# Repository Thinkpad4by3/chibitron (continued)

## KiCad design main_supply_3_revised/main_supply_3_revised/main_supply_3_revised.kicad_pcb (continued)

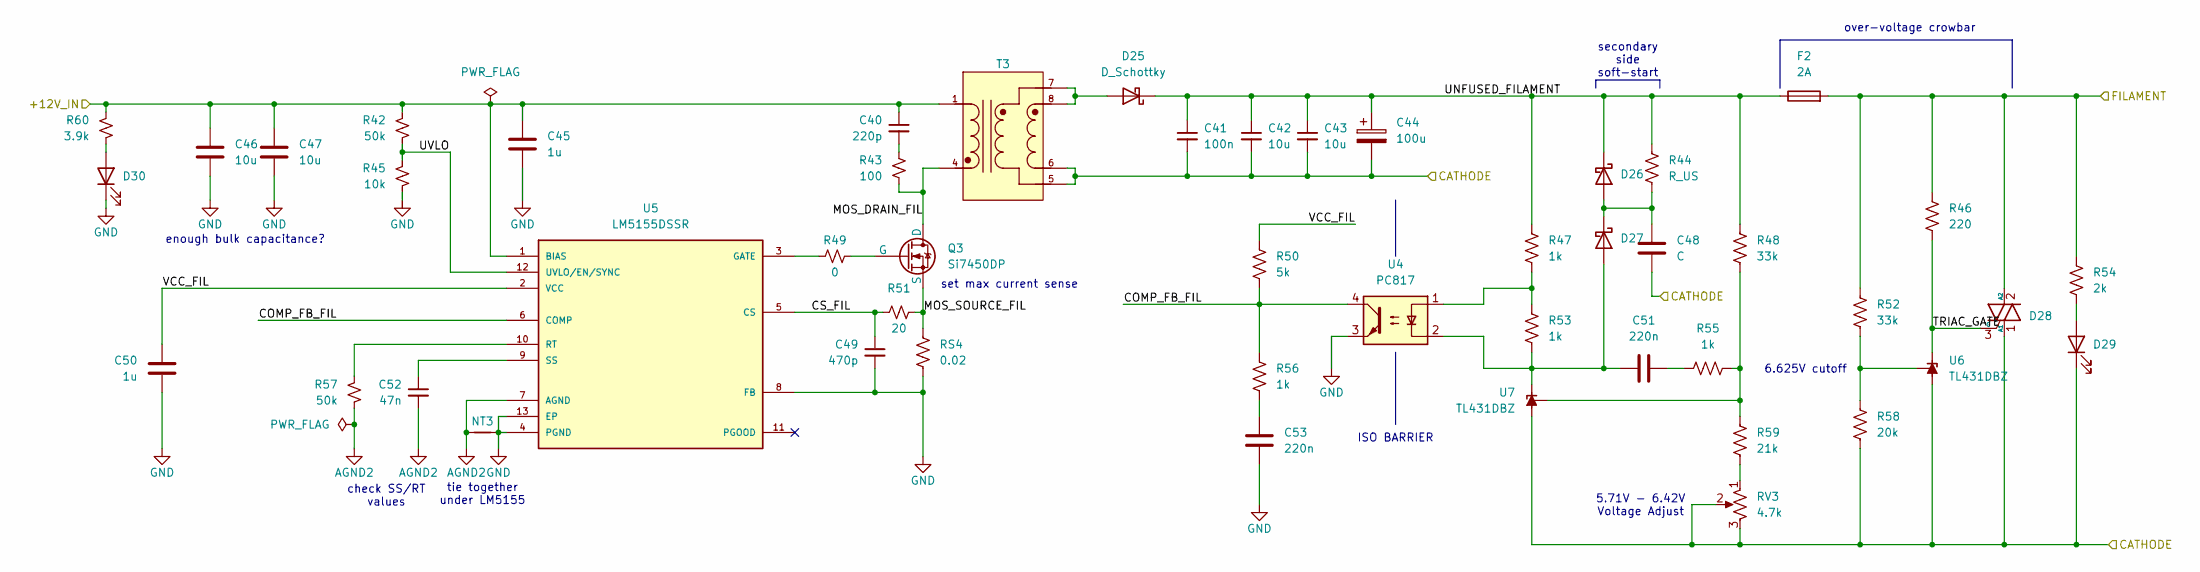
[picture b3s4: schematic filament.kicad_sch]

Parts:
C40: 220p; C_0603_1608Metric
C41: 100n; C_0603_1608Metric
C42, C43, C46, C47: 10u; C_0805_2012Metric
C44: 100u; CP_Elec_6.3x7.7
C45, C50: 1u; C_0603_1608Metric
C48: C; C_0603_1608Metric
C49: 470p; C_0603_1608Metric
C51, C53: 220n; C_0603_1608Metric
C52: 47n; C_0603_1608Metric
D25: D_Schottky; D_SMA
D26, D27: D_Schottky; D_SOD-123
D28: Generic_Triac_A1A2G; SOT-223
D29, D30: LED; LED_0603_1608Metric
F2: 2A; Fuseholder_Littelfuse_Nano2_154x
NT3: NetTie_2; NetTie-2_SMD_Pad0.5mm
Q3: Si7450DP; PowerPAK_SO-8_Single
R42, R57: 50k; R_0603_1608Metric
R43: 100; R_0603_1608Metric
R44: R_US; R_0603_1608Metric
R45: 10k; R_0603_1608Metric
R46: 220; R_0603_1608Metric
R47, R53, R55, R56: 1k; R_0603_1608Metric
R48, R52: 33k; R_0603_1608Metric
R49: 0; R_0603_1608Metric
R50: 5k; R_0603_1608Metric
R51: 20; R_0603_1608Metric
R54: 2k; R_0603_1608Metric
R58: 20k; R_0603_1608Metric
R59: 21k; R_0603_1608Metric
R60: 3.9k; R_0603_1608Metric
RS4: 0.02; R_1206_3216Metric
RV3: 4.7k; Potentiometer_Bourns_3296Y_Vertical
T3: YA9033-ALD; XFMR_YA9033-ALD; PARTREV 05/12/21
U4: PC817; DIP-4_W7.62mm
U5: LM5155DSSR; IC_LM5155DSSR; PARTREV E
U6, U7: TL431DBZ; SOT-23

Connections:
/Filament Supply/+12V_IN: C40.1, C45.1, C46.1, C47.1, R42.1, R60.1, T3.1, U5.1 (BIAS); also elsewhere on the board
/Filament Supply/CATHODE: C41.2, C42.2, C43.2, C44.2, C48.2, D28.1 (A1), D29.1 (K), R58.2, RV3.2, RV3.3, T3.5, T3.6, U6.3 (A), U7.3 (A); also elsewhere on the board
/Filament Supply/COMP_FB_FIL: R50.2, R56.1, U4.4, U5.6 (COMP)
/Filament Supply/CS_FIL: C49.1, R51.1, U5.5 (CS)
/Filament Supply/FILAMENT: D28.2 (A2), F2.2, R46.1, R52.1, R54.1; also elsewhere on the board
/Filament Supply/MOS_DRAIN_FIL: Q3.5 (D), R43.2, T3.4
/Filament Supply/MOS_SOURCE_FIL: Q3.1 (S), Q3.2 (S), Q3.3 (S), R51.2, RS4.1
/Filament Supply/TRIAC_GATE: D28.3 (G), R46.2, U6.1 (K)
/Filament Supply/UNFUSED_FILAMENT: C41.1, C42.1, C43.1, C44.1, D25.1 (K), D26.1 (K), F2.1, R44.1, R47.1, R48.1
/Filament Supply/UVLO: R42.2, R45.1, U5.12 (UVLO/EN/SYNC)
/Filament Supply/VCC_FIL: C50.1, R50.1, U5.2 (VCC)
AGND2: C52.2, NT3.1, R57.2, U5.7 (AGND)
GND: C45.2, C46.2, C47.2, C49.2, C50.2, C53.2, D30.1 (K), NT3.2, R45.2, RS4.2, U4.3, U5.4 (PGND), U5.8 (FB), U5.13 (EP); also elsewhere on the board
unnamed: C40.2, R43.1
unnamed: C51.2, R55.1
unnamed: C53.1, R56.2
unnamed: D25.2 (A), T3.7, T3.8
unnamed: C48.1, D26.2 (A), D27.1 (K), R44.2
unnamed: C51.1, D27.2 (A), R53.2, U4.2, U7.1 (K)
unnamed: D29.2 (A), R54.2
unnamed: D30.2 (A), R60.2
unnamed: Q3.4 (G), R49.2
unnamed: R47.2, R53.1, U4.1
unnamed: R59.2, RV3.1
unnamed: R49.1, U5.3 (GATE)
unnamed: R57.1, U5.10 (RT)
unnamed: C52.1, U5.9 (SS)
unnamed: R52.2, R58.1, U6.2 (REF)
unnamed: R48.2, R55.2, R59.1, U7.2 (REF)

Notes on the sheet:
set max current sense
tie together under LM5155
check SS/RT values
secondary side soft-start
ISO BARRIER
enough bulk capacitance?
6.625V cutoff
5.71V - 6.42V Voltage Adjust
over-voltage crowbar

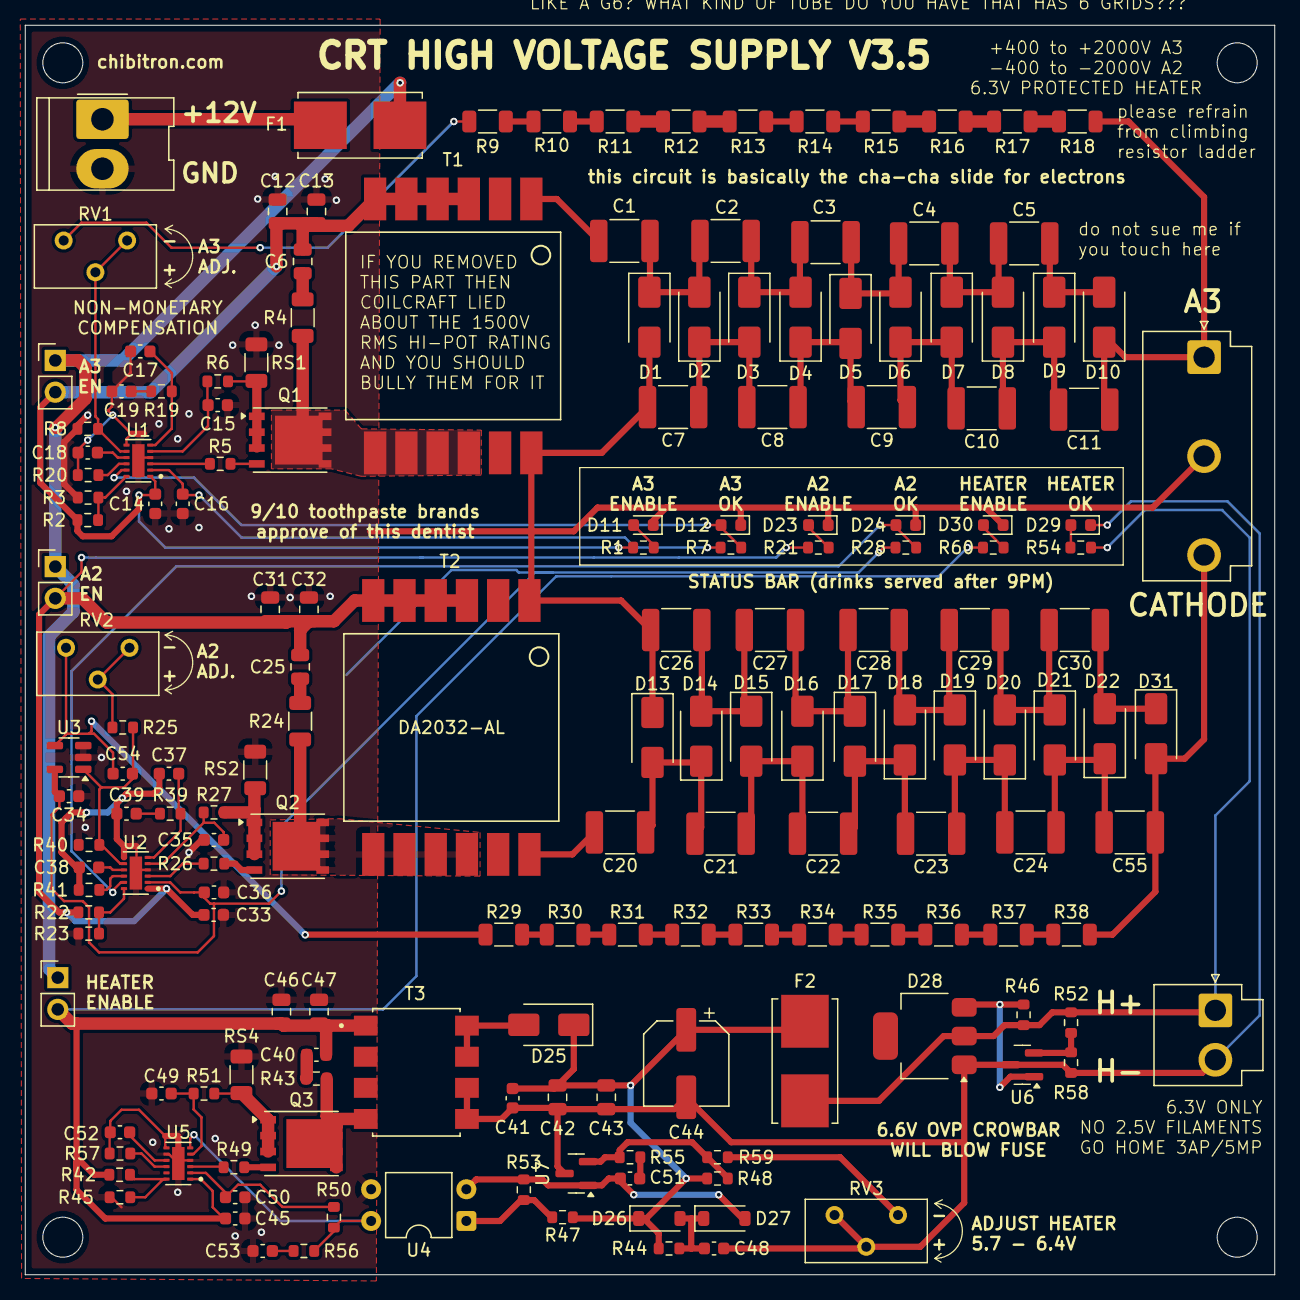
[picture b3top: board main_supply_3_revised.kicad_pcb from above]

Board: 2 copper layers, 100.0 x 100.0 mm, 176 parts (0 on the bottom side), 109 nets.

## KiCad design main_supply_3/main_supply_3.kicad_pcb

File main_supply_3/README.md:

## CRT High Voltage Gen.2 

## Status
- Completed, succeeded by main_supply_3_revised
- I would not recommend building this board

##  Design & Architecture 
The architecture was re-thought out from scratch over the previous supply. With the LM5180, they tended to work quite well, however they did have a bit of a major downside....regulation. Under extremely light load, the voltage would soar, and under very heavy load or it would tend to compensate by increasing the output voltage. Given the method of regulation is feedback sensing through the primary side, and high ratio step-up transformers are known for poor leakage inductance, the sensing ability of the converter could be quite poor at times. (See notes on Gen.1 V2 for more info on this)

Another reasons for ditching the LM5180 was due to was due to wanting variable output voltage, and the LM5180 uses a single resistor Rfb to determine this voltage. Not just did this require alot of tweaking, but provided no good method for changing the voltage with some level of signal control. Going back to a more conventional resistor divider style gave plenty of known proven options for this.

The new design uses an LM5155 and a far more conventional topology. The filament was powered through a TL431 regulated isolated flyback converter, and the A2/A3 generation was done through non-isolated ground referenced converters. A2 was referenced to ground, so the A2 supply generated the cathode potential at -400 - 2000V, and A3 was just the positive copy of A2. The main HV supplies use the NA5920-ALD, the only >1:10 ratio transformer available at the moment that is 

1) easily available
2) supports a >1000V HiPOT rating.

You might ask how I planned on getting 2000V out of a (barely) 1000V transformer. Well I'm going to use a voltage multiplier to just multiply the output by 3X. Seems like a good idea....cockroft-walton multipliers have been a proven choice of high-voltage generation for nearly a century. Well, we will get back to this in a bit. The exact topology follows the "boost mode style" found in a few LiDAR supplies and the like, which means that the charge pump caps are seperate from the filter caps, and the filter caps are larger. Otherwise, it operates the same way. Rough calculations say that 3x multiplier @ 2000V should keep the primary side at ~700V even at max voltage, should be fine for a 1500Vrms rated transformer. Primary side spiking thanks to the large 1:24 ratio would be kept at a meager 30V which would allow the choice of some more common low-voltage FETs.

Focus Amplifier was a somewhat odd design. As found on previous designs, the standard focus ladder stack was limiting for larger tubes. The highest voltage potentiometer easily available is 500V, and some larger tubes (7JP/7VP series) takes nearly 1kV on A1. The design was tested in LTspice, and validated in circuit. I did revise it for the next version, since the method of creating an isolated voltage was quite convoluted and featured poor regulation as beam current increased. It was beneficial that the focus voltage was now on the primary side, low voltage control.

## Troubleshooting & Bring-up 
The bring-up of this supply was quite troublesome. The main issue being that I did not realize the true nature of voltage-multiplied flybacks, being that they conduct on both halves of the cycle. This becomes a much bigger problem when you realize that reflected impedance is squared of the turns ratio, so the 12mA or so peak current on the secondary side becomes almost 7A on the primary side. The converter, running in current mode control, sees 7A and immediately trips, so it fails to actually regulate anything and just kinda bubbles with tiny little bursts. This is enough to get to sort of develop and open-load voltage but under load it just dies. 

To combat this, I dug up my transformer stock and found some 1:10 that would just about fit in its place. This would reduce my primary current during the forward mode of the supply to 1.2A, which was enough to sneak it past the 4A primary side current limit. Regulation still wasn't great, as evidenced by the screaming sound the supply made, but was able to supply 2W to a 2Mohm load which was excellent. Further tweaking of R/C COMP values helped. 

Among the main fault, a bunch of small issues that I found include the following:

- Wrong value resistors for the feedback chain for 400-2.1kV - A2
- Increase soft-start capacitance
- Transformer wrong: switch to Wurth 10:1 part
- MOSFET too low voltage: need >200V part
- Fix layout to not have GND overlapping underneath transformer
- Add RC filtering to A2,A3 + LC filtering to Filament
- Change TLV314 to TLV237, check >6.8V operation
- Fix the 20 ohm resistors in the VM’s to be in the correct spot
- Add soft start to filament supply 
- Capacitively couple feedback -> test this (only on A3)
- Change the RC filtering?? 2/2n + 100ohm & 1k R slope comp.
- Change connectors and remove focus amp from power supply side.
- Re-layout and silkscreen
- Add large input cap and filtering 
- UVLO resistors configured incorrectly to disable on low-voltage - 10k lower
- Fix diode on filament to be Schottky not HV rectifier
- Add 220n + 2k resistor on A2
- Add interlock if no power to op amp -> no A2 supply?
- ADD POWER TO THE AMPLIFIER FOR A2 FEEDBACK
- Wrong sense resistor values for Current sense - 0.02ohm
- Wrong value resistors for the feedback chain for 400-2.1kV - A3
- Opto feedback wired up wrong - fix

## Learnings
Hugely better understand of secondary side regulated Flyback converters and voltage multipliers

Output needs to be filtered 

Class-A style focus amp works great

Good architecture, continue developing.

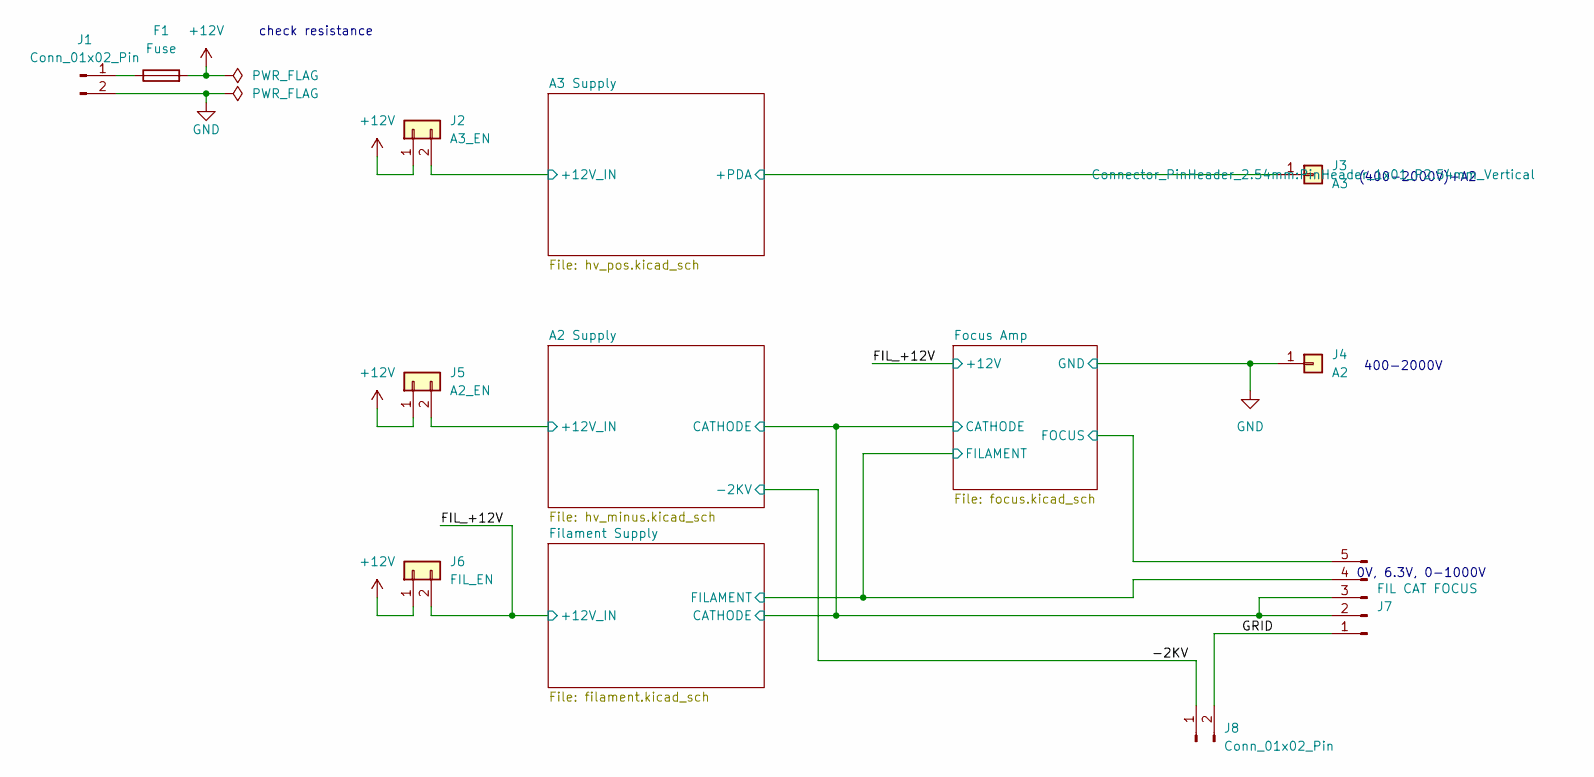
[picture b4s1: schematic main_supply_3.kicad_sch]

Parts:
F1: Fuse; Fuse_0805_2012Metric
J1: Conn_01x02_Pin; Molex_KK-396_5273-02A_1x02_P3.96mm_Vertical
J2: A3_EN; PinHeader_1x02_P2.54mm_Vertical
J3: A3; PinHeader_1x01_P2.54mm_Vertical
J4: A2; PinHeader_1x01_P2.54mm_Vertical
J5: A2_EN; PinHeader_1x02_P2.54mm_Vertical
J6: FIL_EN; PinHeader_1x02_P2.54mm_Vertical
J7: FIL CAT FOCUS; Molex_KK-396_5273-05A_1x05_P3.96mm_Vertical
J8: Conn_01x02_Pin; PinHeader_1x02_P2.54mm_Vertical

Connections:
+12V: F1.2, J2.1, J5.1, J6.1
/-2KV: J8.1; also elsewhere on the board
/A2 Supply/+12V_IN: J5.2; also elsewhere on the board
/A2 Supply/CATHODE: J7.2, J7.3; also elsewhere on the board
/A3 Supply/+12V_IN: J2.2; also elsewhere on the board
/A3 Supply/+PDA: J3.1; also elsewhere on the board
/FIL_+12V: J6.2; also elsewhere on the board
/Filament Supply/FILAMENT: J7.4; also elsewhere on the board
/Focus Amp/FOCUS: J7.5; also elsewhere on the board
/GRID: J7.1, J8.2
GND: J1.2, J4.1; also elsewhere on the board
unnamed: F1.1, J1.1

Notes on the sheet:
(400-2000V)+A2
400-2000V
0V, 6.3V, 0-1000V
check resistance

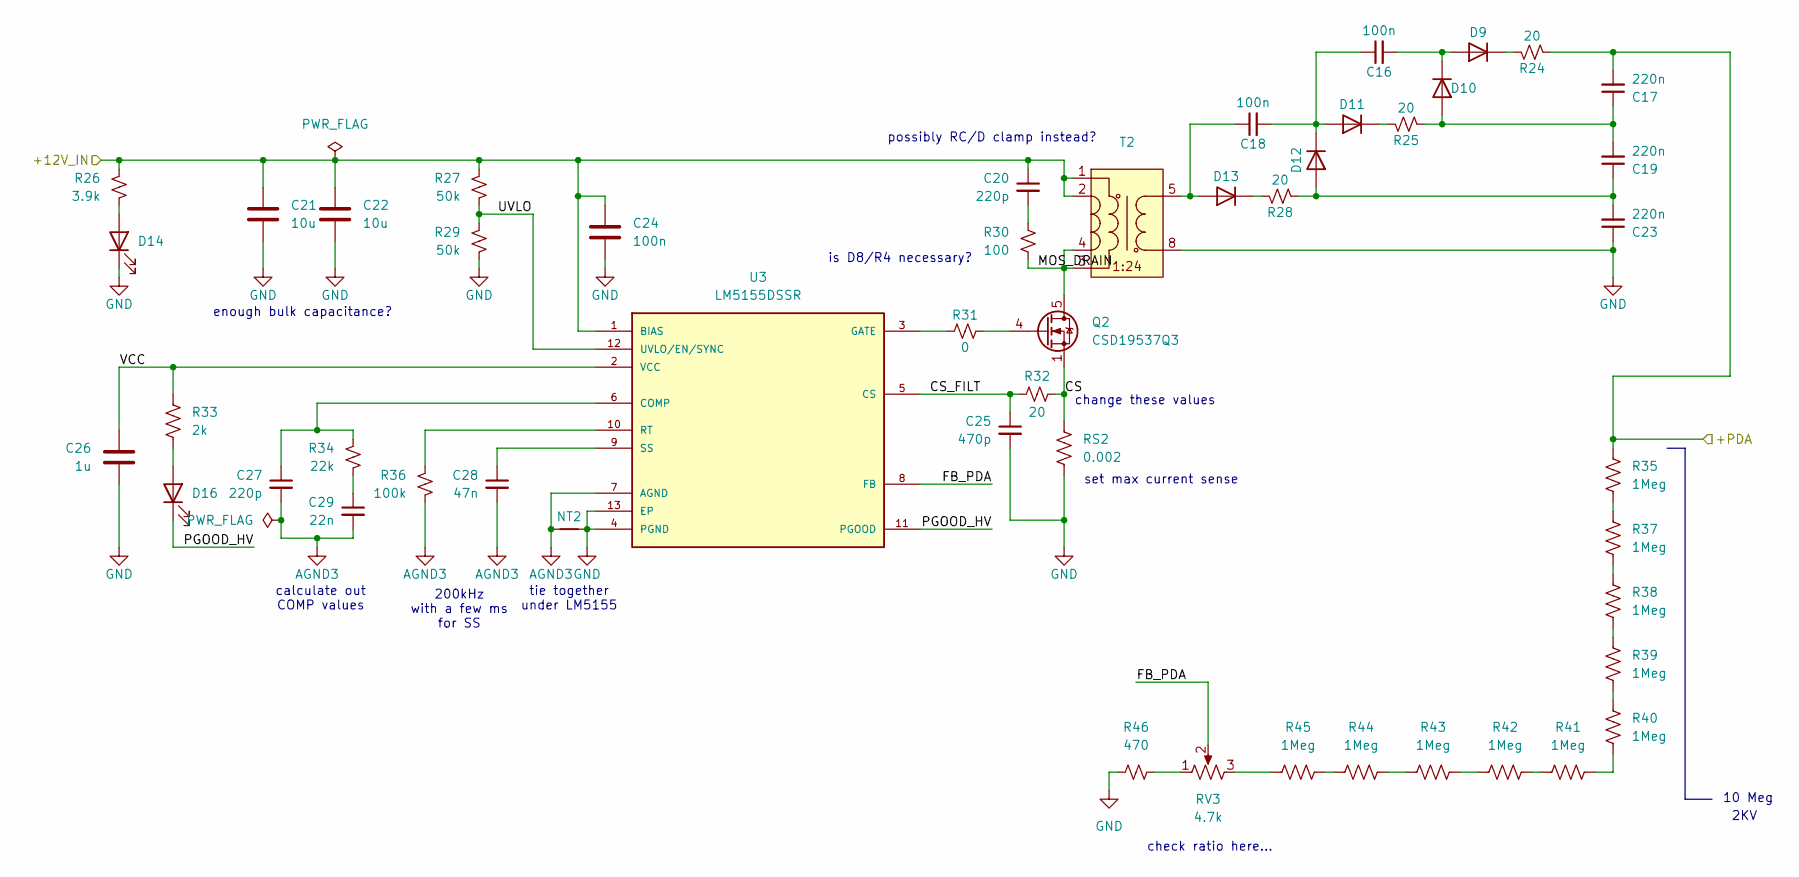
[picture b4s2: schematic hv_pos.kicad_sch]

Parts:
C16, C18: 100n; C_1812_4532Metric
C17, C19, C23: 220n; C_2220_5750Metric
C20, C27: 220p; C_0603_1608Metric
C21, C22: 10u; C_0805_2012Metric
C24: 100n; C_0603_1608Metric
C25: 470p; C_0603_1608Metric
C26: 1u; C_0603_1608Metric
C28: 47n; C_0603_1608Metric
C29: 22n; C_0603_1608Metric
D9, D10, D11, D12, D13: D; D_SMA
D14, D16: LED; LED_0603_1608Metric
NT2: NetTie_2; NetTie-2_SMD_Pad0.5mm
Q2: CSD19537Q3; VSON-8_3.3x3.3mm_P0.65mm_NexFET
R24, R25, R28: 20; R_1206_3216Metric
R26: 3.9k; R_0603_1608Metric
R27, R29: 50k; R_0603_1608Metric
R30: 100; R_0603_1608Metric
R31: 0; R_0603_1608Metric
R32: 20; R_0603_1608Metric
R33: 2k; R_0603_1608Metric
R34: 22k; R_0603_1608Metric
R35, R37, R38, R39, R40, R41, R42, R43, R44, R45: 1Meg; R_1206_3216Metric
R36: 100k; R_0603_1608Metric
R46: 470; R_0603_1608Metric
RS2: 0.002; R_1206_3216Metric
RV3: 4.7k; Potentiometer_Bourns_3296W_Vertical
T2: NA5920-AL
U3: LM5155DSSR; IC_LM5155DSSR; PARTREV E

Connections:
/A3 Supply/+12V_IN: C20.1, C21.1, C22.1, C24.1, R26.1, R27.1, T2.1, T2.2, U3.1 (BIAS); also elsewhere on the board
/A3 Supply/+PDA: C17.2, R24.2, R35.1; also elsewhere on the board
/A3 Supply/CS: Q2.1 (S), Q2.2 (S), Q2.3 (S), R32.2, RS2.1
/A3 Supply/CS_FILT: C25.1, R32.1, U3.5 (CS)
/A3 Supply/FB_PDA: RV3.2, U3.8 (FB)
/A3 Supply/MOS_DRAIN: Q2.5 (D), R30.2, T2.3, T2.4
/A3 Supply/PGOOD_HV: D16.1 (K), U3.11 (PGOOD)
/A3 Supply/UVLO: R27.2, R29.1, U3.12 (UVLO/EN/SYNC)
/A3 Supply/VCC: C26.1, R33.1, U3.2 (VCC)
AGND3: C27.2, C28.2, C29.2, NT2.1, R36.2, U3.7 (AGND)
GND: C21.2, C22.2, C23.1, C24.2, C25.2, C26.2, D14.1 (K), NT2.2, R29.2, R46.1, RS2.2, T2.8, U3.4 (PGND), U3.13 (EP); also elsewhere on the board
unnamed: C20.2, R30.1
unnamed: C29.1, R34.2
unnamed: D9.1 (K), R24.1
unnamed: C17.1, C19.2, D10.2 (A), R25.2
unnamed: C16.2, D9.2 (A), D10.1 (K)
unnamed: C16.1, C18.2, D11.2 (A), D12.1 (K)
unnamed: D11.1 (K), R25.1
unnamed: C19.1, C23.2, D12.2 (A), R28.2
unnamed: C18.1, D13.2 (A), T2.5
unnamed: D13.1 (K), R28.1
unnamed: D14.2 (A), R26.2
unnamed: D16.2 (A), R33.2
unnamed: Q2.4 (G), R31.2
unnamed: R35.2, R37.1
unnamed: R37.2, R38.1
unnamed: R38.2, R39.1
unnamed: R39.2, R40.1
unnamed: R40.2, R41.2
unnamed: R41.1, R42.2
unnamed: R42.1, R43.2
unnamed: R43.1, R44.2
unnamed: R44.1, R45.2
unnamed: R45.1, RV3.3
unnamed: R46.2, RV3.1
unnamed: C27.1, R34.1, U3.6 (COMP)
unnamed: R31.1, U3.3 (GATE)
unnamed: R36.1, U3.10 (RT)
unnamed: C28.1, U3.9 (SS)

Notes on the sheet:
check ratio here...
2KV
enough bulk capacitance?
calculate out COMP values
is D8/R4 necessary?
possibly RC/D clamp instead?
10 Meg
tie together under LM5155
change these values
set max current sense
200kHz with a few ms for SS

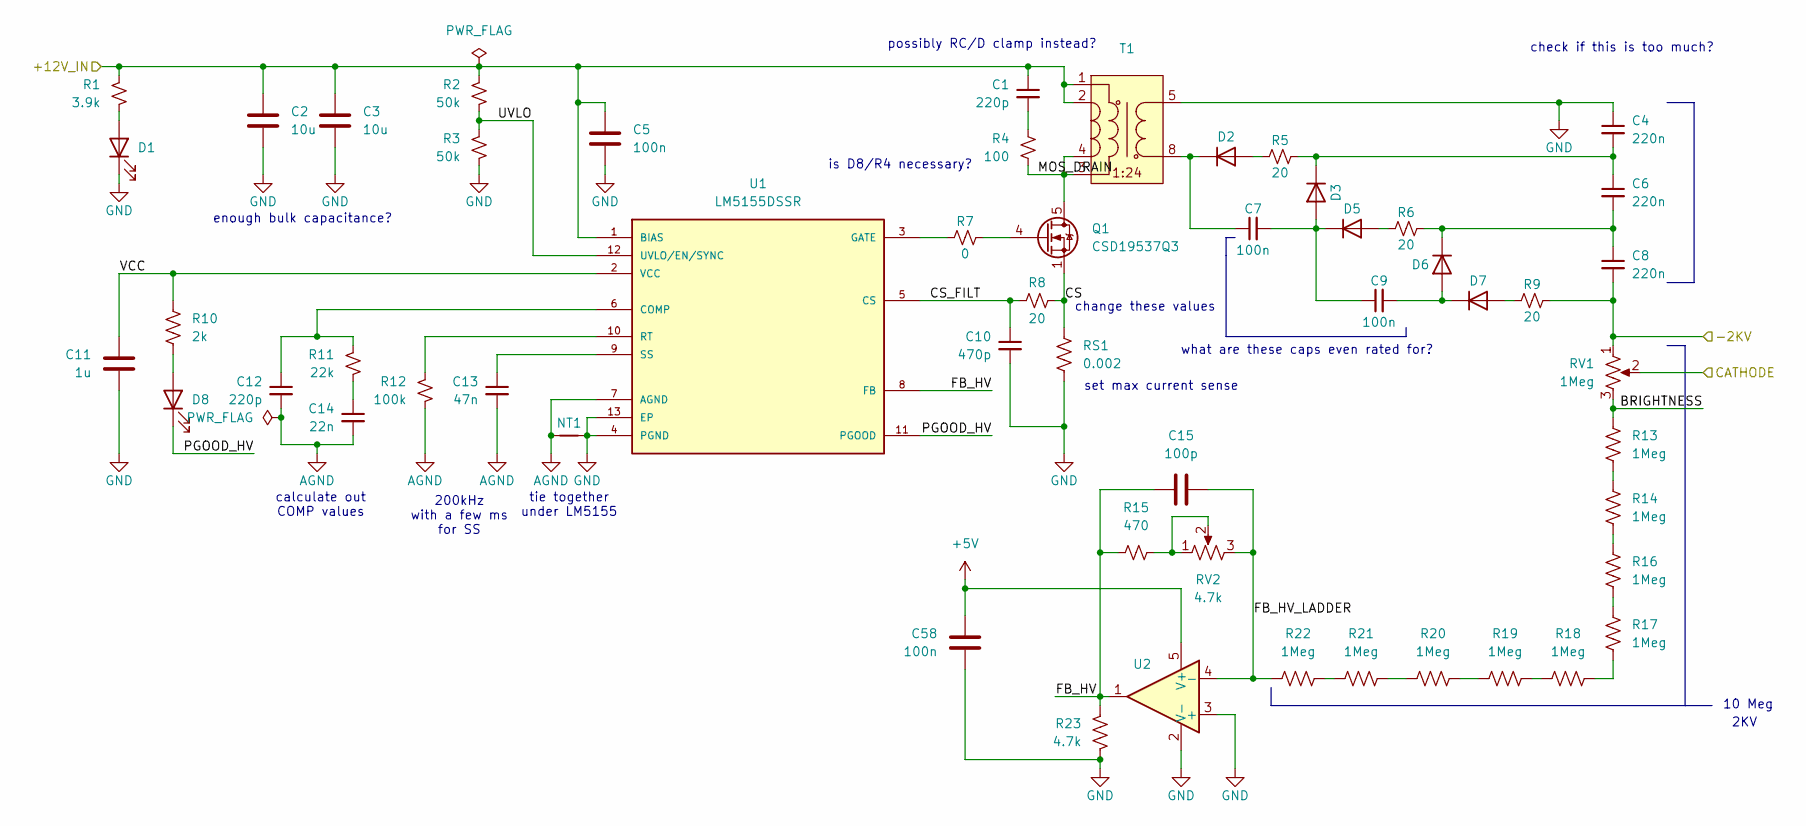
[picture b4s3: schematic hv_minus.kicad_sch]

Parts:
C1, C12: 220p; C_0603_1608Metric
C2, C3: 10u; C_0805_2012Metric
C4, C6, C8: 220n; C_2220_5750Metric
C5, C58: 100n; C_0603_1608Metric
C7, C9: 100n; C_1812_4532Metric
C10: 470p; C_0603_1608Metric
C11: 1u; C_0603_1608Metric
C13: 47n; C_0603_1608Metric
C14: 22n; C_0603_1608Metric
C15: 100p; C_0603_1608Metric
D1, D8: LED; LED_0603_1608Metric
D2, D3, D5, D6, D7: D; D_SMA
NT1: NetTie_2; NetTie-2_SMD_Pad0.5mm
Q1: CSD19537Q3; VSON-8_3.3x3.3mm_P0.65mm_NexFET
R1: 3.9k; R_0603_1608Metric
R2, R3: 50k; R_0603_1608Metric
R4: 100; R_0603_1608Metric
R5, R6, R9: 20; R_1206_3216Metric
R7: 0; R_0603_1608Metric
R8: 20; R_0603_1608Metric
R10: 2k; R_0603_1608Metric
R11: 22k; R_0603_1608Metric
R12: 100k; R_0603_1608Metric
R13, R14, R16, R17, R18, R19, R20, R21, R22: 1Meg; R_1206_3216Metric
R15: 470; R_0603_1608Metric
R23: 4.7k; R_0603_1608Metric
RS1: 0.002; R_1206_3216Metric
RV1: 1Meg; Potentiometer_Bourns_3296W_Vertical
RV2: 4.7k; Potentiometer_Bourns_3296W_Vertical
T1: NA5920-AL
U1: LM5155DSSR; IC_LM5155DSSR; PARTREV E
U2: TLV314QDBVR; SOT-23-5

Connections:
+5V: C58.1, U2.5 (V+); also elsewhere on the board
/-2KV: C8.2, R9.2, RV1.1; also elsewhere on the board
/A2 Supply/+12V_IN: C1.1, C2.1, C3.1, C5.1, R1.1, R2.1, T1.1, T1.2, U1.1 (BIAS); also elsewhere on the board
/A2 Supply/BRIGHTNESS: R13.1, RV1.3
/A2 Supply/CATHODE: RV1.2; also elsewhere on the board
/A2 Supply/CS: Q1.1 (S), Q1.2 (S), Q1.3 (S), R8.2, RS1.1
/A2 Supply/CS_FILT: C10.1, R8.1, U1.5 (CS)
/A2 Supply/FB_HV: C15.1, R15.1, R23.1, U1.8 (FB), U2.1
/A2 Supply/FB_HV_LADDER: C15.2, R22.1, RV2.3, U2.4 (-)
/A2 Supply/MOS_DRAIN: Q1.5 (D), R4.2, T1.3, T1.4
/A2 Supply/PGOOD_HV: D8.1 (K), U1.11 (PGOOD)
/A2 Supply/UVLO: R2.2, R3.1, U1.12 (UVLO/EN/SYNC)
/A2 Supply/VCC: C11.1, R10.1, U1.2 (VCC)
AGND: C12.2, C13.2, C14.2, NT1.1, R12.2, U1.7 (AGND)
GND: C2.2, C3.2, C4.1, C5.2, C10.2, C11.2, C58.2, D1.1 (K), NT1.2, R3.2, R23.2, RS1.2, T1.5, U1.4 (PGND), U1.13 (EP), U2.2 (V-), U2.3 (+); also elsewhere on the board
unnamed: C1.2, R4.1
unnamed: C14.1, R11.2
unnamed: D1.2 (A), R1.2
unnamed: D2.2 (A), R5.1
unnamed: C7.1, D2.1 (K), T1.8
unnamed: C7.2, C9.1, D3.2 (A), D5.1 (K)
unnamed: C4.2, C6.1, D3.1 (K), R5.2
unnamed: D5.2 (A), R6.1
unnamed: C9.2, D6.2 (A), D7.1 (K)
unnamed: C6.2, C8.1, D6.1 (K), R6.2
unnamed: D7.2 (A), R9.1
unnamed: D8.2 (A), R10.2
unnamed: Q1.4 (G), R7.2
unnamed: R13.2, R14.1
unnamed: R14.2, R16.1
unnamed: R15.2, RV2.1, RV2.2
unnamed: R16.2, R17.1
unnamed: R17.2, R18.2
unnamed: R18.1, R19.2
unnamed: R19.1, R20.2
unnamed: R20.1, R21.2
unnamed: R21.1, R22.2
unnamed: C12.1, R11.1, U1.6 (COMP)
unnamed: R7.1, U1.3 (GATE)
unnamed: R12.1, U1.10 (RT)
unnamed: C13.1, U1.9 (SS)

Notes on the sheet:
tie together under LM5155
is D8/R4 necessary?
10 Meg
change these values
check if this is too much?
set max current sense
2KV
200kHz with a few ms for SS
enough bulk capacitance?
calculate out COMP values
what are these caps even rated for?
possibly RC/D clamp instead?

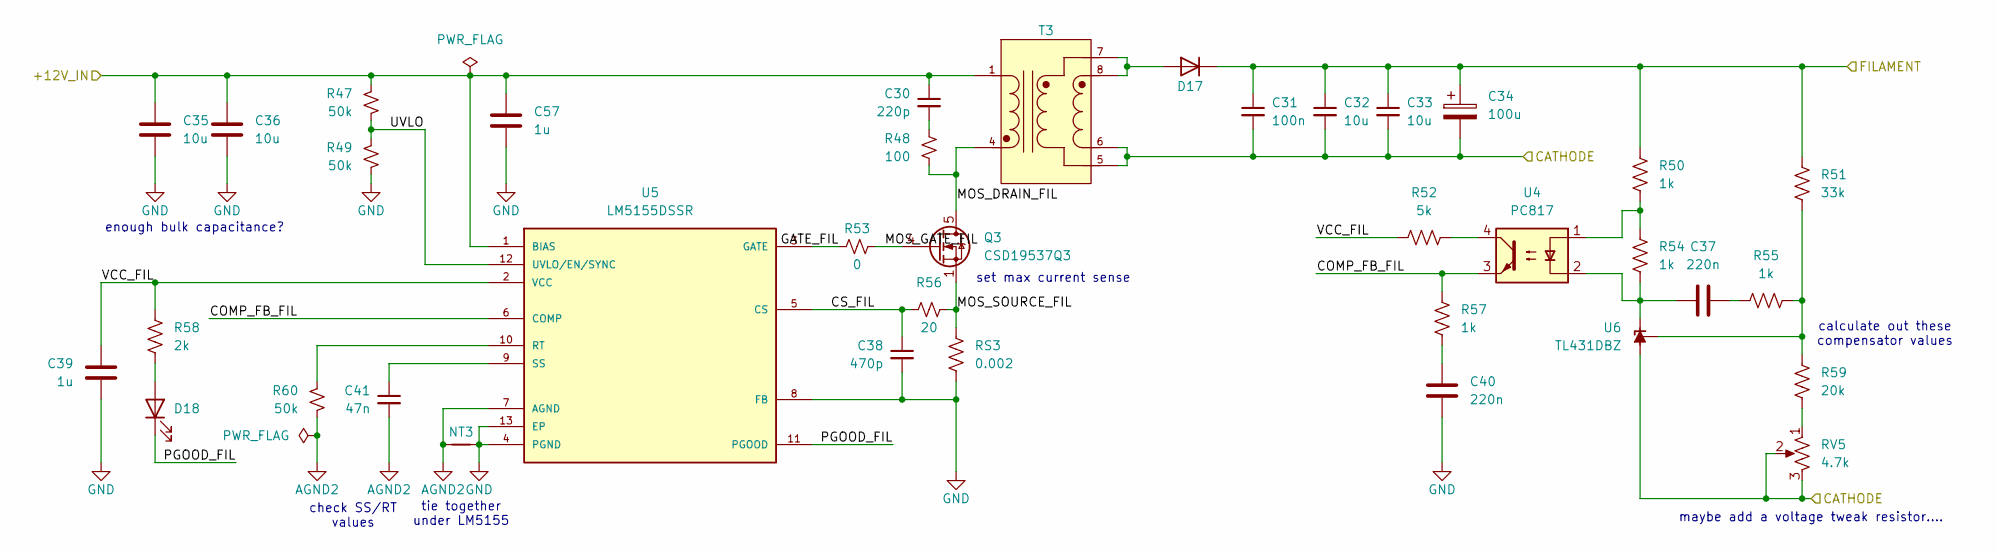
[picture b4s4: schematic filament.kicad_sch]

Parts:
C30: 220p; C_0603_1608Metric
C31: 100n; C_0603_1608Metric
C32, C33, C35, C36: 10u; C_0805_2012Metric
C34: 100u; CP_Elec_6.3x7.7
C37, C40: 220n; C_0603_1608Metric
C38: 470p; C_0603_1608Metric
C39, C57: 1u; C_0603_1608Metric
C41: 47n; C_0603_1608Metric
D17: D; D_SMA
D18: LED; LED_0603_1608Metric
NT3: NetTie_2; NetTie-2_SMD_Pad0.5mm
Q3: CSD19537Q3; VSON-8_3.3x3.3mm_P0.65mm_NexFET
R47, R49, R60: 50k; R_0603_1608Metric
R48: 100; R_0603_1608Metric
R50, R54, R55, R57: 1k; R_0603_1608Metric
R51: 33k; R_0603_1608Metric
R52: 5k; R_0603_1608Metric
R53: 0; R_0603_1608Metric
R56: 20; R_0603_1608Metric
R58: 2k; R_0603_1608Metric
R59: 20k; R_0603_1608Metric
RS3: 0.002; R_1206_3216Metric
RV5: 4.7k; Potentiometer_Bourns_3296W_Vertical
T3: YA9033-ALD; XFMR_YA9033-ALD; PARTREV 05/12/21
U4: PC817; DIP-4_W7.62mm
U5: LM5155DSSR; IC_LM5155DSSR; PARTREV E
U6: TL431DBZ; SOT-23

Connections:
/A2 Supply/CATHODE: C31.2, C32.2, C33.2, C34.2, RV5.2, RV5.3, T3.5, T3.6, U6.3 (A); also elsewhere on the board
/FIL_+12V: C30.1, C35.1, C36.1, C57.1, R47.1, T3.1, U5.1 (BIAS); also elsewhere on the board
/Filament Supply/COMP_FB_FIL: R57.1, U4.3, U5.6 (COMP)
/Filament Supply/CS_FIL: C38.1, R56.1, U5.5 (CS)
/Filament Supply/FILAMENT: C31.1, C32.1, C33.1, C34.1, D17.1 (K), R50.1, R51.1; also elsewhere on the board
/Filament Supply/GATE_FIL: R53.1, U5.3 (GATE)
/Filament Supply/MOS_DRAIN_FIL: Q3.5 (D), R48.2, T3.4
/Filament Supply/MOS_GATE_FIL: Q3.4 (G), R53.2
/Filament Supply/MOS_SOURCE_FIL: Q3.1 (S), Q3.2 (S), Q3.3 (S), R56.2, RS3.1
/Filament Supply/PGOOD_FIL: D18.1 (K), U5.11 (PGOOD)
/Filament Supply/UVLO: R47.2, R49.1, U5.12 (UVLO/EN/SYNC)
/Filament Supply/VCC_FIL: C39.1, R52.1, R58.1, U5.2 (VCC)
AGND2: C41.2, NT3.1, R60.2, U5.7 (AGND)
GND: C35.2, C36.2, C38.2, C39.2, C40.2, C57.2, NT3.2, R49.2, RS3.2, U5.4 (PGND), U5.8 (FB), U5.13 (EP); also elsewhere on the board
unnamed: C30.2, R48.1
unnamed: C37.2, R55.1
unnamed: C40.1, R57.2
unnamed: D17.2 (A), T3.7, T3.8
unnamed: D18.2 (A), R58.2
unnamed: R50.2, R54.1, U4.1
unnamed: R52.2, U4.4
unnamed: R59.2, RV5.1
unnamed: R60.1, U5.10 (RT)
unnamed: C41.1, U5.9 (SS)
unnamed: C37.1, R54.2, U4.2, U6.1 (K)
unnamed: R51.2, R55.2, R59.1, U6.2 (REF)

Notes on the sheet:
set max current sense
tie together under LM5155
calculate out these compensator values
maybe add a voltage tweak resistor....
check SS/RT values
enough bulk capacitance?

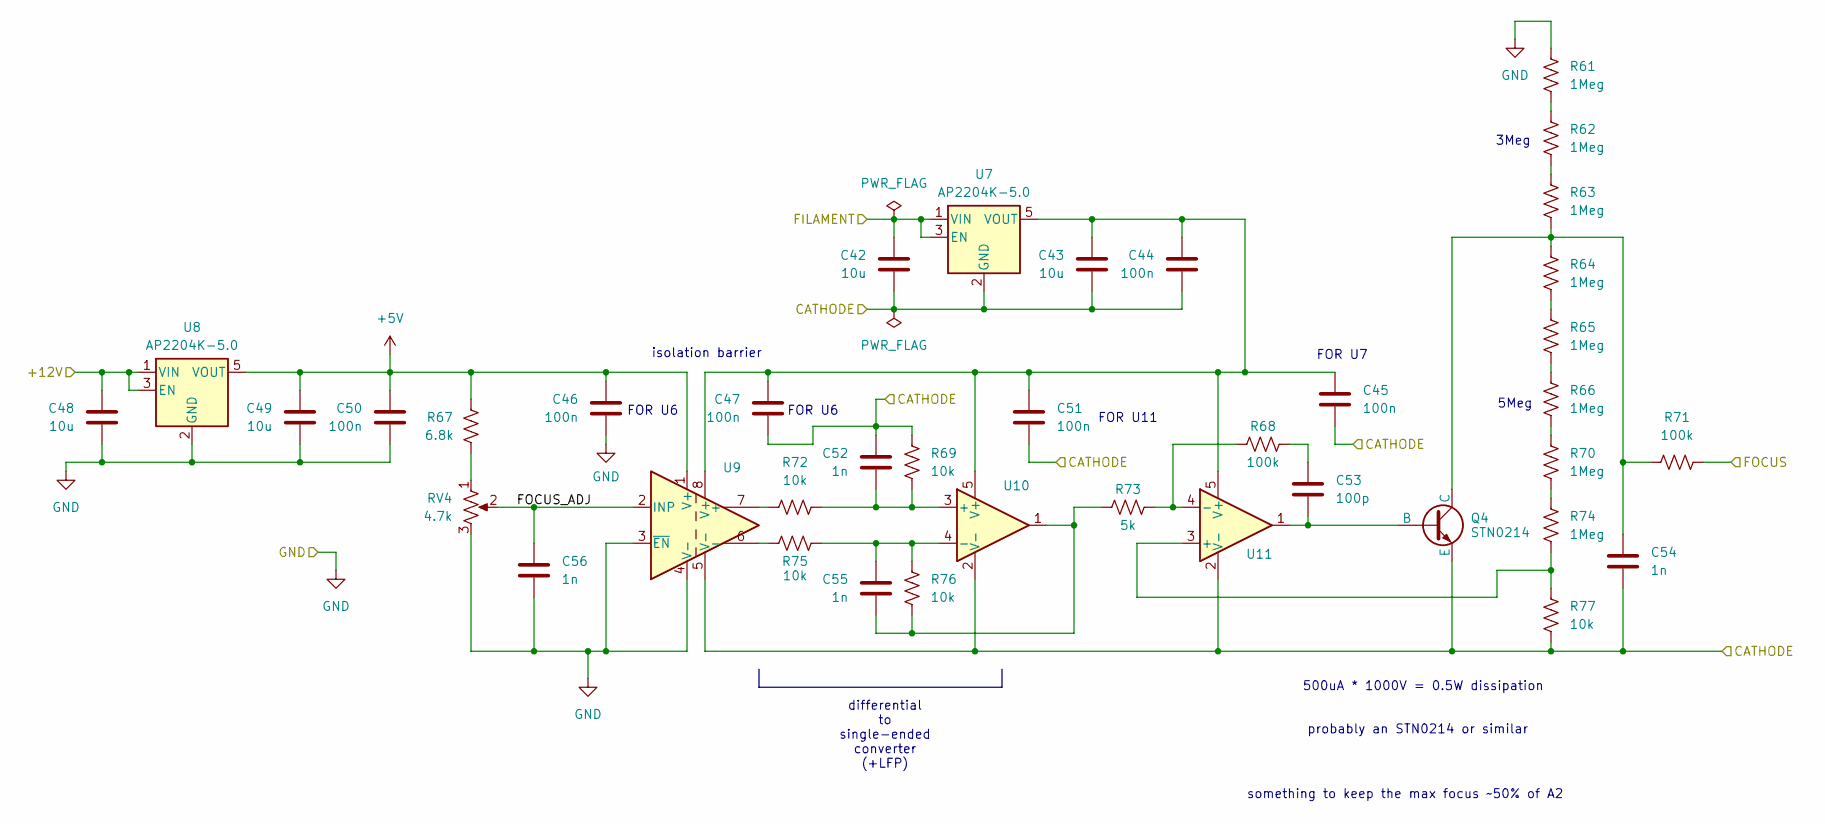
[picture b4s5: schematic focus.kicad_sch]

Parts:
C42, C43, C48, C49: 10u; C_0805_2012Metric
C44, C45, C46, C47, C50, C51: 100n; C_0603_1608Metric
C52, C55, C56: 1n; C_0603_1608Metric
C53: 100p; C_0603_1608Metric
C54: 1n; C_1206_3216Metric
Q4: STN0214; SOT-223-3_TabPin2
R61, R62, R63, R64, R65, R66, R70, R74: 1Meg; R_1206_3216Metric
R67: 6.8k; R_0603_1608Metric
R68: 100k; R_0603_1608Metric
R69, R72, R75, R76, R77: 10k; R_0603_1608Metric
R71: 100k; R_1206_3216Metric
R73: 5k; R_0603_1608Metric
RV4: 4.7k; Potentiometer_Bourns_3296W_Vertical
U7, U8: AP2204K-5.0; SOT-23-5
U9: AMC1311; SOIC-8_7.5x5.85mm_P1.27mm
U10, U11: TLV314QDBVR; SOT-23-5

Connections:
+5V: C46.1, C49.1, C50.1, R67.1, U8.5 (VOUT), U9.1 (V+); also elsewhere on the board
/A2 Supply/CATHODE: C42.2, C43.2, C44.2, C45.2, C47.2, C51.2, C52.1, C54.2, Q4.3 (E), R69.1, R77.2, U7.2 (GND), U9.5 (V-), U10.2 (V-), U11.2 (V-); also elsewhere on the board
/FIL_+12V: C48.1, U8.1 (VIN), U8.3 (EN); also elsewhere on the board
/Filament Supply/FILAMENT: C42.1, U7.1 (VIN), U7.3 (EN); also elsewhere on the board
/Focus Amp/FOCUS: R71.2; also elsewhere on the board
/Focus Amp/FOCUS_ADJ: C56.1, RV4.2, U9.2 (INP)
GND: C46.2, C48.2, C49.2, C50.2, C56.2, R61.1, RV4.3, U8.2 (GND), U9.3 (~EN), U9.4 (V-); also elsewhere on the board
unnamed: C53.1, R68.2
unnamed: C55.2, R73.1, R76.2, U10.1
unnamed: C53.2, Q4.2 (B), U11.1
unnamed: C54.1, Q4.1 (C), R63.2, R64.1, R71.1
unnamed: R61.2, R62.1
unnamed: R62.2, R63.1
unnamed: R64.2, R65.1
unnamed: R65.2, R66.1
unnamed: R66.2, R70.1
unnamed: R67.2, RV4.1
unnamed: R70.2, R74.1
unnamed: R72.1, U9.7 (+)
unnamed: R75.1, U9.6 (-)
unnamed: C52.2, R69.2, R72.2, U10.3 (+)
unnamed: C55.1, R75.2, R76.1, U10.4 (-)
unnamed: C43.1, C44.1, C45.1, C47.1, C51.1, U7.5 (VOUT), U9.8 (V+), U10.5 (V+), U11.5 (V+)
unnamed: R74.2, R77.1, U11.3 (+)
unnamed: R68.1, R73.2, U11.4 (-)

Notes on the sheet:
isolation barrier
probably an STN0214 or similar
differential to single-ended converter (+LFP)
something to keep the max focus ~50% of A2
FOR U11
3Meg
FOR U7
FOR U6
500uA * 1000V = 0.5W dissipation
5Meg

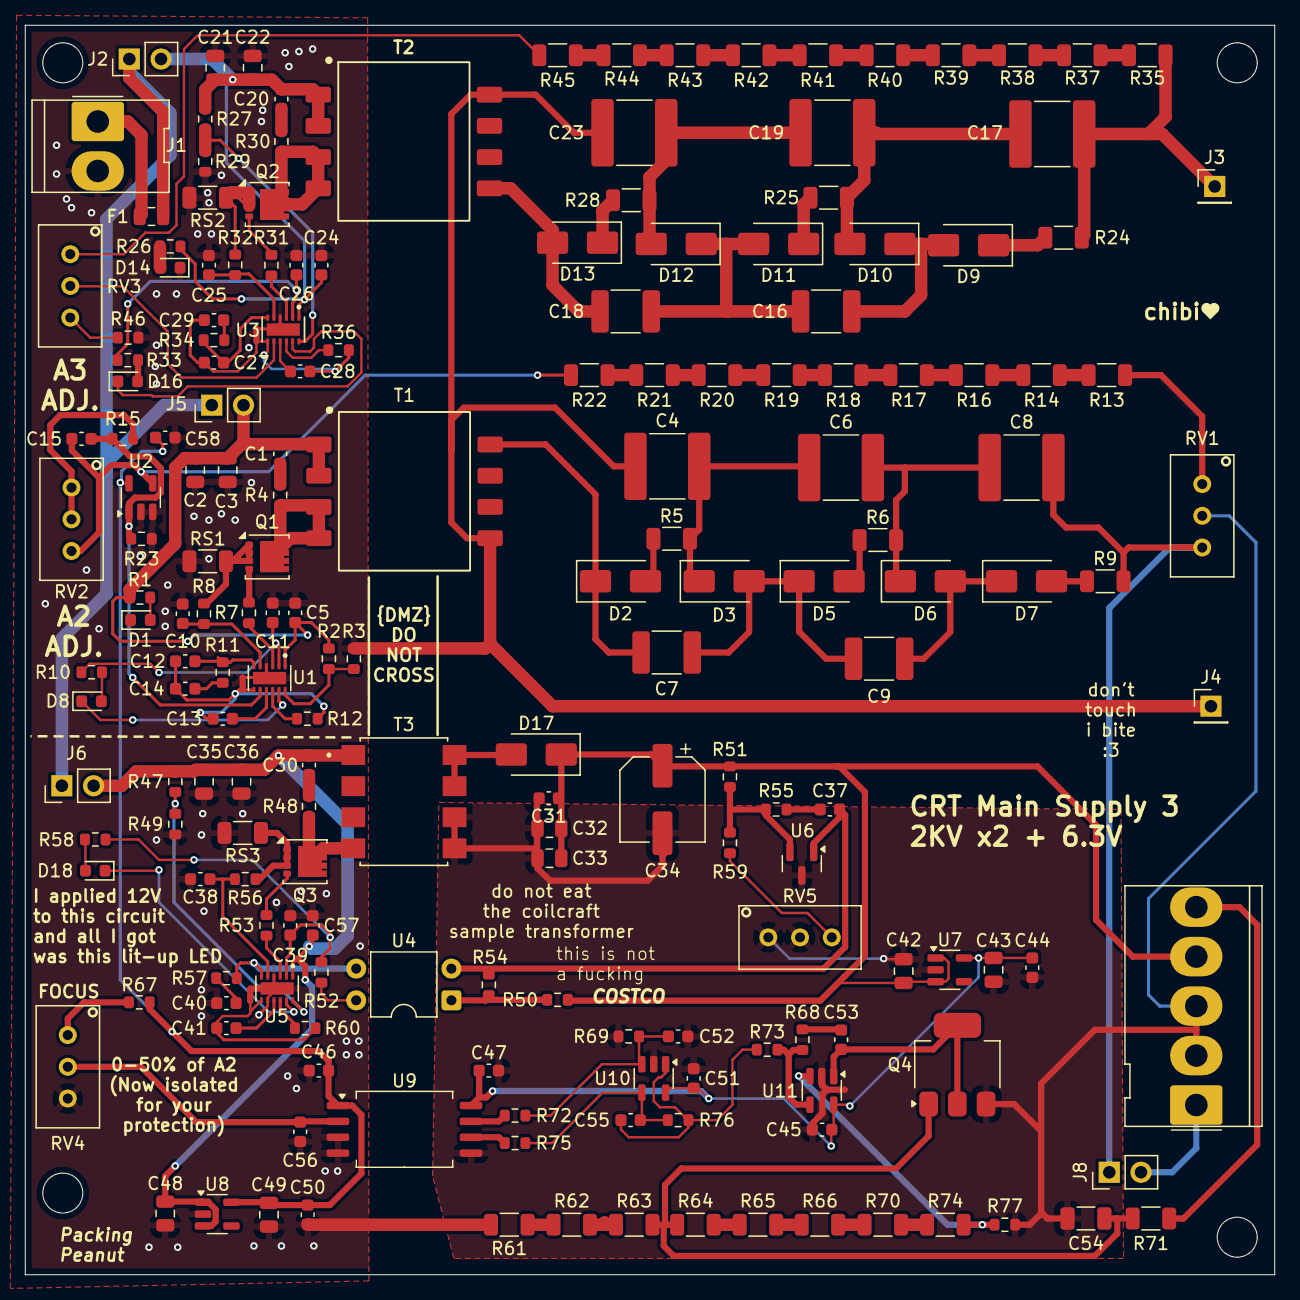
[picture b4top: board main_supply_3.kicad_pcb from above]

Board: 2 copper layers, 100.0 x 100.0 mm, 189 parts (0 on the bottom side), 126 nets.
